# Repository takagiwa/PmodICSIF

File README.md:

# PmodICSIF

Next project is here https://github.com/takagiwa/PmodBDServoIF

----

This is an ICS interface Pmod project.

ICS (Interactive Communication System) specification is developped by Kondo Kagaku.

Pmod Standard is developped by Digilent.

This hardware based on ICS変換基板 ( https://kondo-robot.com/product/03121 ) ICS_adapter_manual.pdf .

# References

ICS変換基板 https://kondo-robot.com/product/03121

Pmod Standard https://reference.digilentinc.com/reference/pmod/specification

テクニカルガイド https://kondo-robot.com/archives/faq_category/tecguide

ICS3.6と3.5の違いと新機能についての紹介 https://kondo-robot.com/faq/ics3_6function

シリアルサーボ制御方法（１）　回路編 https://kondo-robot.com/faq/serial-servo-method-tech

# Bill of materials

| Ref | Parts |
----|----
| J1 | Pmod |
| J2 | JST B2P-VH 2x3.96mm_Vertical |
| IC3 | SN74LV1T125DBVR |
| IC6 | SN74LV1T125DBVR |
| IC4 | SN74LV1T125DBVR |
| IC7 | SN74LV1T125DBVR |
| IC1 | SN74LV1T125DBVR |
| IC2 | SN74LV1T125DBVR |
| IC5 | OnSemi MC7805CDTRKG |
| D1 | LED (1206) |
| D2 | LED (1206) |
| R1 | 330ohm (1206) |
| R2 | 330ohm (1206) |
| C3 | Nichicon UWP1HR33MCL1GB ( 0.33µF 50V Aluminum Electrolytic Capacitors Radial, Can - SMD  ) |
| C4 | 0.1u (1206) |
| C6 | 0.1u (1206) |
| C1 | 0.1u (1206) |
| C5 | 0.1u (1206) |
| C7 | 0.1u (1206) |
| C2 | 0.1u (1206) |
| J4 | Samtec:SL-103-X-XX_1x03 |
| J3 | Samtec:SL-103-X-XX_1x03 |
| R5 | 2.2k (1206) |
| R6 | 2.2k (1206) |
| D3 | Zener (0805) |
| D4 | Zener (0805) |
| R4 | 2.2k (1206) |
| R3 | 2.2k (1206) |

SN74LV1T125DBVR

SN74AUC1GU04DBVR

https://www.digikey.jp/product-detail/ja/jst-sales-america-inc/B2P-VH-LF-SN/455-1639-ND/926547
https://www.digikey.jp/product-detail/ja/texas-instruments/SN74LV1T125DBVR/296-37172-1-ND/4555589
https://www.digikey.jp/product-detail/ja/texas-instruments/SN74AUC1GU04DBVR/296-13174-1-ND/484297
https://www.digikey.jp/product-detail/ja/on-semiconductor/MC7805CDTRKG/MC7805CDTRKGOSCT-ND/1967122
https://www.digikey.jp/product-detail/ja/nichicon/UWP1HR33MCL1GB/493-9832-1-ND/3963164
https://www.digikey.jp/products/ja/discrete-semiconductor-products/diodes-zener-single/287?k=&pkeyword=&sv=0&pv252=25&pv69=3&sf=1&FV=mu5.6V%7C920%2C1f140000%2Cmu200mW%7C2109%7C0%2Cffe0011f&quantity=&ColumnSort=0&page=1&stock=1&nstock=1&pageSize=25
https://www.digikey.jp/product-detail/ja/comchip-technology/CZRF52C5V6/641-1062-1-ND/1121184
https://www.digikey.jp/product-detail/ja/te-connectivity-amp-connectors/86479-4/A28786-ND/353097
https://www.digikey.jp/product-detail/ja/stackpole-electronics-inc/RMCF1206JT330R/RMCF1206JT330RCT-ND/1942777
https://www.digikey.jp/product-detail/ja/wurth-electronics-inc/885012208058/732-8109-1-ND/5454736
https://www.digikey.jp/product-detail/ja/broadcom-limited/HSMN-C150/516-1446-1-ND/637770
https://www.digikey.jp/product-detail/ja/broadcom-limited/HSMC-C150/516-2825-1-ND/3909257
https://www.digikey.jp/product-detail/ja/sullins-connector-solutions/PRPC003SFAN-RC/S1211EC-03-ND/2775371

あとはサーボをつなぐコネクタ、LED、R、C

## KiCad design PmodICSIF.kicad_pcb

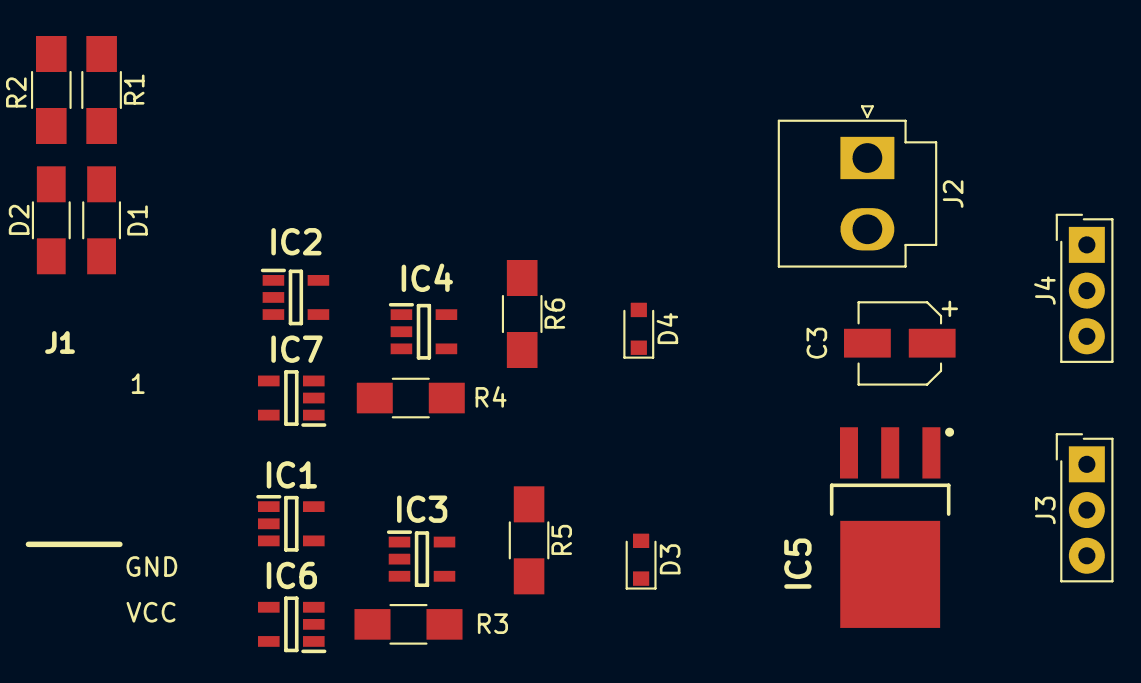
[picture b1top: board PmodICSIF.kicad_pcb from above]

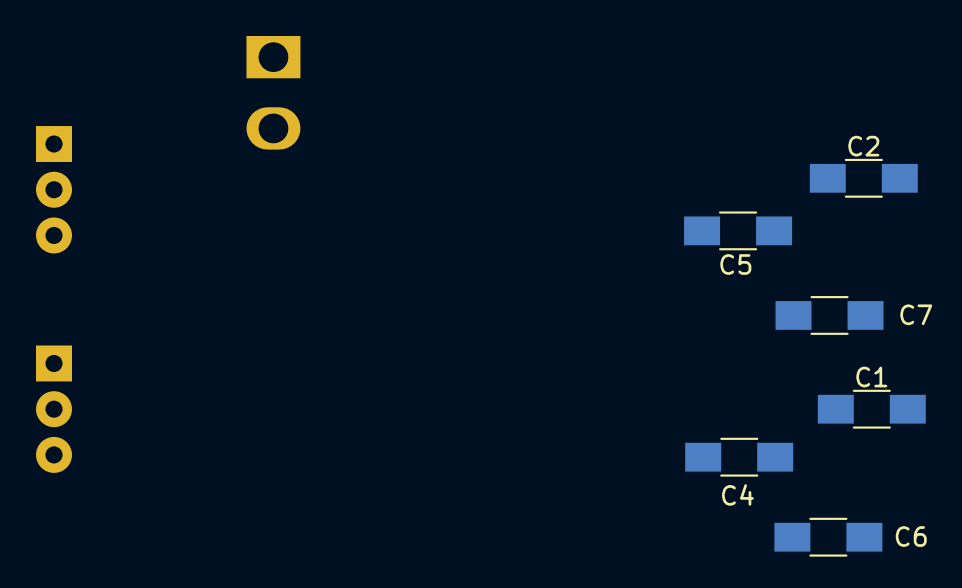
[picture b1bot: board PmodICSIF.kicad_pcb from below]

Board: 2 copper layers, 28 parts (6 on the bottom side), 14 nets, no tracks yet.

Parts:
C1, C2, C4, C5, C6, C7: 0.1u; C_1206_HandSoldering
C3: 0.33u; CP_Elec_4x4.5
D1, D2: LED; C_1206_HandSoldering
D3, D4: D_Zener; D_0805
IC1, IC2, IC3, IC4, IC6, IC7: SN74LV1T125DBVR; SOT95P280X145-5N
IC5: MC7805CDTRKG; TO229P990X238-4N
J1: Conn_02x06_Top_Bottom; pmod_pin_array_6x2
J2: Conn_01x02; JST_VH_B2P-VH_2x3.96mm_Vertical
J3, J4: Conn_01x03; SL-103-X-XX_1x03
R1, R2: 330; R_1206_HandSoldering
R3, R4, R5, R6: 2.2k; R_1206_HandSoldering

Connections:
+5V: C4.1, C5.1, IC3.5, IC4.5, IC5.3, R5.1, R6.1
/EN_IN0: IC2.2, IC7.1
/EX_IN1: IC1.2, IC6.1
GND: C1.2, C2.2, C3.2, C4.2, C5.2, C6.2, C7.2, D3.2, D4.2, IC1.3, IC2.3, IC3.3, IC4.3, IC5.2, IC5.4, IC6.3, IC7.3, J2.2, J3.3, J4.3
unnamed: D1.2, R1.2
unnamed: D2.2, R2.2
unnamed: D3.1, IC3.4, J3.1, R3.1, R5.2
unnamed: D4.1, IC4.4, J4.1, R4.1, R6.2
unnamed: IC1.4, IC3.1
unnamed: IC2.4, IC4.1
unnamed: IC6.2, R3.2
unnamed: IC7.2, R4.2
VCC: C1.1, C2.1, C6.1, C7.1, IC1.5, IC2.5, IC6.5, IC7.5, R1.1, R2.1
VDDA: C3.1, IC5.1, J2.1, J3.2, J4.2

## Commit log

2019-07-06 modify readme
2019-07-06 initial schematics
2019-07-06 add board file
2019-07-07 drawed
2019-07-07 first ordered version
2019-10-02 とりあえず
2019-10-02 とりあえずテンプレートを追加
2019-10-04 送信部分ができたところ。
2019-10-04 受信側も入れた。
2019-10-04 FIFO もひとまず作ってみた。
2019-10-04 擬似コードを書いた。
2019-10-08 レジスタ側を uart primitive に合わせて改造。 uart primitive 側は送信部分を書いた。受信部分はコーディング中。
2019-10-09 コアに送受信を組み込み、折り返したデータが取れた。 ただホスト側インタフェースをどう制御するか問題が残っている。
2019-10-13 IP をまとめてブロックダイアグラムまでつくった
2019-10-14 IP を作り直し。
2019-10-14 GPIO アクセスはできて、恐らくサーボへの送信もできた（フラグが立っている）けど何も受信していない模様。
2019-10-22 ジャンパ追加して受信できるようになった。
2019-10-22 角度と読み書きのワードの相互変換の関数を入れた。
2019-10-22 fix BOM table
2019-10-22 fix table again
